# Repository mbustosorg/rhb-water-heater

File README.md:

Red Hot Beverly Water Heater
============================

Controls the water bath's solenoid valve from a DS18B20 in the bath, reads
the loop pressure, and drives a four digit HT16K33 display.  CircuitPython on
a Waveshare ESP32-S3-ETH at 192.168.1.9, wired; there is no WiFi.

The heater relay (`heater_pin`, IO47) is initialised low and never driven;
the heater is controlled elsewhere.

OSC messages
------------

Every address has one producer.  `/pressure` is consumed here, never
re-broadcast.

| Address | Direction | Payload |
| --- | --- | --- |
| `/temperature` | out | Bath temperature, deg F.  The only temperature on the network |
| `/water_heater` | out | Valve open/shut.  Named for the heater it used to switch |
| `/upper_temp`, `/lower_temp` | out | Configured valve setpoints, deg F |
| `/water_pressure` | out | Bath loop pressure, PSI |
| `/pressure` | in, from rhb-sensor-monitor | Accumulator pressure, PSI, rounded |

The outbound messages go every 5 s, in that order, to `MOBILE_CLIENTS`.  Keep
`/water_pressure` last: rhb-sensor-monitor writes its `water_*.csv` row when
it arrives.

microosc dispatches on `startswith`, so `propane_pressure_handler` re-checks
the address to ignore `/pressure_fine`.

Display
-------

| Digits | Shows |
| --- | --- |
| 0-1 | Accumulator pressure, from `/pressure` |
| 2-3 | Bath temperature, blinking while the valve is open |

`--` means no data.

Configuration
-------------

`config_rhb.json`, gitignored.

| Key | Meaning |
| --- | --- |
| `IP` | This device's static address |
| `MOBILE_CLIENTS` | Comma separated listeners, `host` or `host:port` (body display is `192.168.1.3:10002`) |
| `UPPER_TEMP` | Valve shuts at or above, deg F |
| `LOWER_TEMP` | Valve opens at or below, deg F |

Never call `set_dhcp()`: the rig has no DHCP, and it blocks the event loop,
valve included, waiting for a lease.

A listener that fails, usually an absent phone, is skipped for a growing
number of cycles.

Valve control
-------------

| Condition | Action |
| --- | --- |
| Temperature at or below `LOWER_TEMP` | Valve opens |
| Temperature at or above `UPPER_TEMP` | Valve shuts |
| Between the two | No change |
| No usable temperature reading | Valve shuts |

Readings outside 33-212F are discarded; a missing probe used to read as 0F.

The old ten minute recycle safety shutdown policed the heater, which this
board no longer owns, so it was removed.

Hardware
--------

| Pin | Use |
| --- | --- |
| IO47 | Heater SSR, not driven |
| IO48 | Valve SSR |
| IO3 | Safety shutdown SSR |
| IO1 | Loop pressure, analogue |
| IO15 | OneWire, DS18B20 bath probe |
| IO38 / IO39 | I2C SCL / SDA, HT16K33 display |

Powered by PoE alone, on a carrier board; the SSRs are off the board.  See
[HARDWARE.md](HARDWARE.md) and [kicad/](kicad/README.md).  **Set
`PRESSURE_DIVIDER` in `code.py` to 1.5 when the carrier goes in.**

The probe runs at 9 bit: readings are used as whole degrees, and 12 bit
blocks the event loop 750 ms per read instead of 94 ms.

Deployment
----------

Copy `code.py`, `rhb_utils.py` and `config_rhb.json` to `CIRCUITPY`.  The
board soft reboots on write and the relay pins initialise off.

Console: `/dev/cu.usbmodem<UID>` (`cu.*`, not `tty.*`, so DTR is not
asserted).  A healthy board prints `Temperature: NN` about every 5 s.

Known rough edges
-----------------

- `/water_heater` and `state["heater_status"]` report the valve, kept so
  rhb-sensor-monitor and the body display didn't have to change.
- The valve shuts on any unusable probe reading, and the OneWire bus throws
  CRC errors regularly, so a flaky probe cycles the valve.
- The OneWire bus has also returned an empty scan at boot.  The software
  recovers, but suspect the pull-up, parasite power or cable length first.
- `read_and_display_temp` keeps the last probe on the bus, so a second one is
  ignored.  `scan_probes` logs how many it found.
- The receive path overrides microosc's 1 ms socket timeout and 128 byte
  buffer; either default alone stops `/pressure` arriving.  See `poll_osc`.

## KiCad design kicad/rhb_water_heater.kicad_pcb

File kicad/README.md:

Water Heater Carrier Board
==========================

Two layer, 86.5 x 51.5 mm carrier for the circuit in
[HARDWARE.md](../HARDWARE.md).
Parts: [bom.csv](bom.csv).

- **U1** sits component side up, pin 1 (square pad) top right.  Its RJ45 end
  overhangs the right edge by about 16 mm, clearing the cable and PoE module.
- **Terminals**, along the bottom edge, pin 1 (square pad) on the right:

  | Block | Pins, left to right |
  | --- | --- |
  | J7 `PROBE` | `GND DQ 3V3` |
  | J6 `PRESSURE` | `GND SIG +5V` |
  | J5 `SAFETY`, J4 `HEATER`, J3 `VALVE` | `GND SIG` |

- **J2** is `+ - D C`, matching the backpack.
- Ground is poured on both layers.

Regenerating
------------

Edit the scripts, not the KiCad files, then run `./build.sh`, or
`./build.sh --no-route` to try a layout.  Routing needs Java 17+ and
`~/tools/freerouting-1.9.jar`.

| Expected warning | Why |
| --- | --- |
| `lib_symbol_issues` | Symbols live only in the schematic |
| `extra_footprint` | Mounting holes aren't in the schematic |

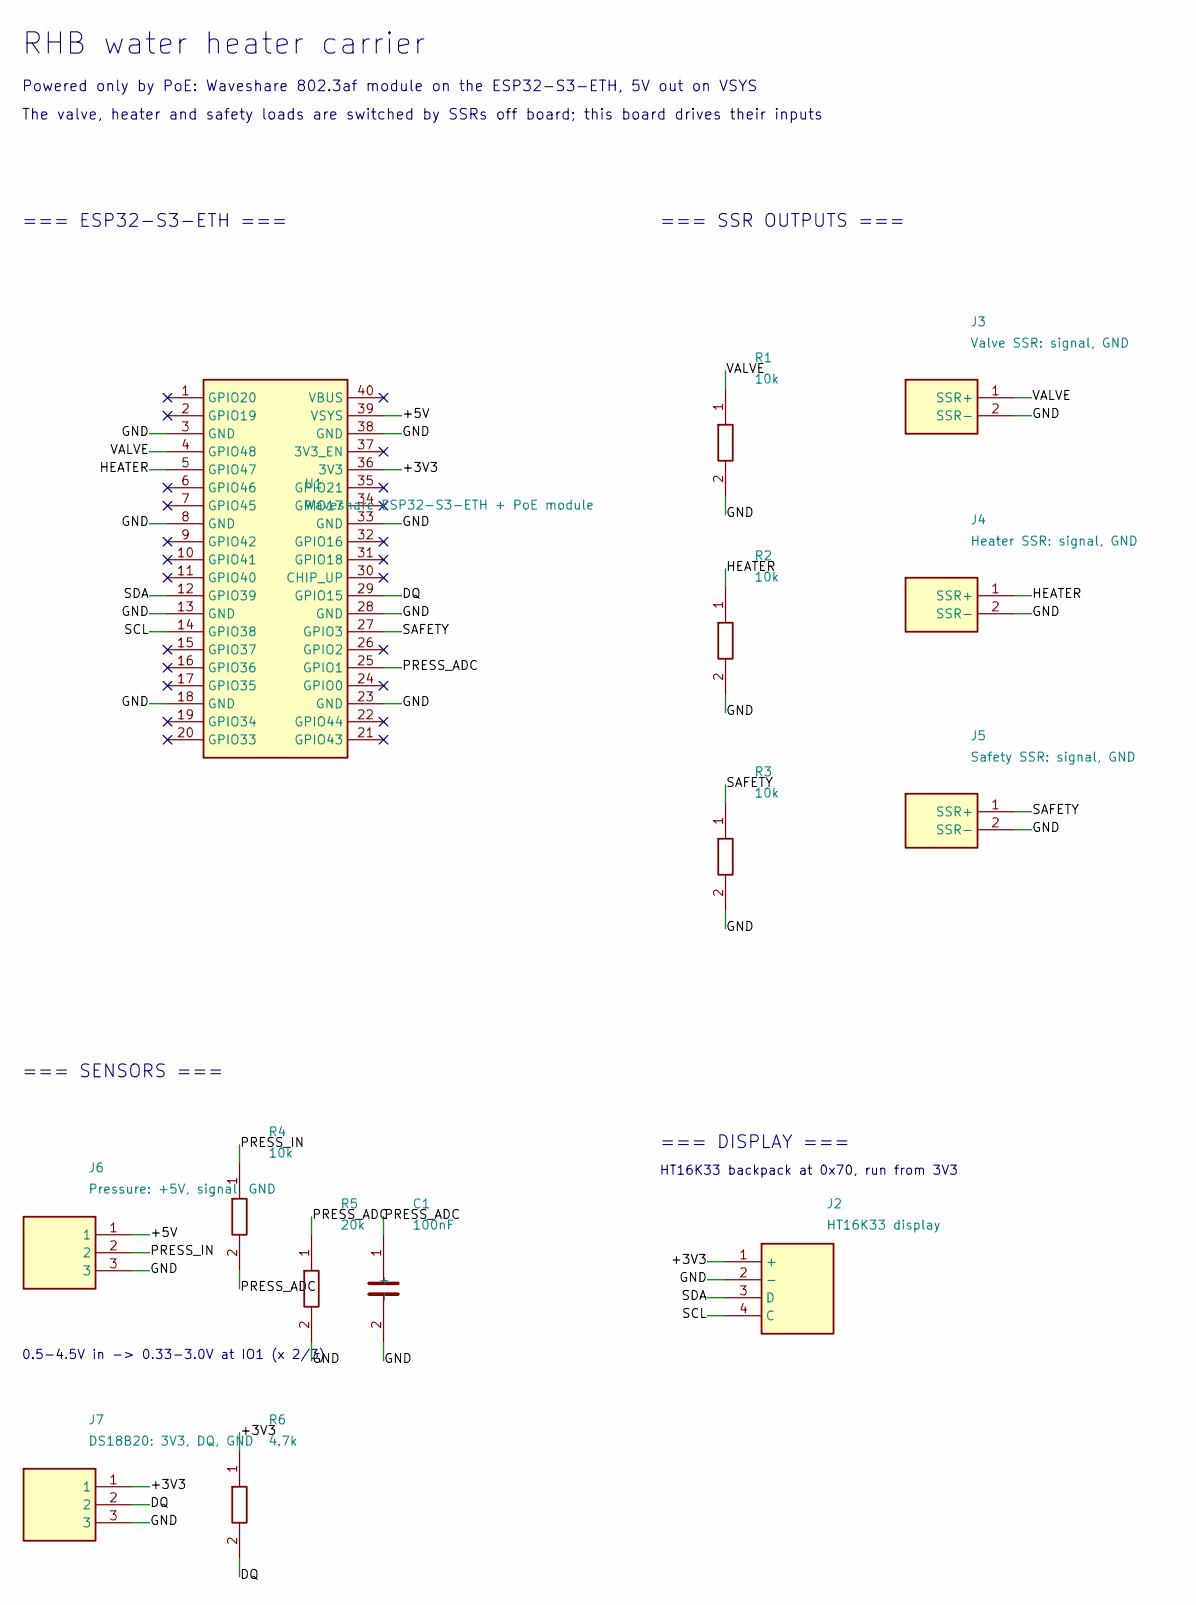
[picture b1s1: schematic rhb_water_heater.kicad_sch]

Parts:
C1: 100nF; C_Disc_D5.0mm_W2.5mm_P5.00mm
J2: HT16K33 display; JST_XH_B4B-XH-A_1x04_P2.50mm_Vertical
J3: Valve SSR: signal, GND; TerminalBlock_Phoenix_MKDS-1,5-2-5.08_1x02_P5.08mm_Horizont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
J4: Heater SSR: signal, GND; TerminalBlock_Phoenix_MKDS-1,5-2-5.08_1x02_P5.08mm_Horizont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
J5: Safety SSR: signal, GND; TerminalBlock_Phoenix_MKDS-1,5-2-5.08_1x02_P5.08mm_Horizont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
J6: Pressure: +5V, signal, GND; TerminalBlock_Phoenix_MKDS-1,5-3-5.08_1x03_P5.08mm_Horizont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
J7: DS18B20: 3V3, DQ, GND; TerminalBlock_Phoenix_MKDS-1,5-3-5.08_1x03_P5.08mm_Horizont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
R1, R2, R3, R4: 10k; R_Axial_DIN0207_L6.3mm_D2.5mm_P2.54mm_Vertical
R5: 20k; R_Axial_DIN0207_L6.3mm_D2.5mm_P2.54mm_Vertical
R6: 4.7k; R_Axial_DIN0207_L6.3mm_D2.5mm_P2.54mm_Vertical
U1: Waveshare ESP32-S3-ETH + PoE module; Waveshare_ESP32-S3-ETH_Socketed

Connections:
/+3V3: J2.1 (+), J7.1, R6.1, U1.36 (3V3)
/+5V: J6.1, U1.39 (VSYS)
/DQ: J7.2, R6.2, U1.29 (GPIO15)
/GND: C1.2 (-), J2.2 (-), J3.2 (SSR-), J4.2 (SSR-), J5.2 (SSR-), J6.3, J7.3, R1.2, R2.2, R3.2, R5.2, U1.3 (GND), U1.8 (GND), U1.13 (GND), U1.18 (GND), U1.23 (GND), U1.28 (GND), U1.33 (GND), U1.38 (GND)
/HEATER: J4.1 (SSR+), R2.1, U1.5 (GPIO47)
/PRESS_ADC: C1.1 (+), R4.2, R5.1, U1.25 (GPIO1)
/PRESS_IN: J6.2, R4.1
/SAFETY: J5.1 (SSR+), R3.1, U1.27 (GPIO3)
/SCL: J2.4 (C), U1.14 (GPIO38)
/SDA: J2.3 (D), U1.12 (GPIO39)
/VALVE: J3.1 (SSR+), R1.1, U1.4 (GPIO48)

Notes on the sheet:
RHB water heater carrier
Powered only by PoE: Waveshare 802.3af module on the ESP32-S3-ETH, 5V out on VSYS
The valve, heater and safety loads are switched by SSRs off board; this board drives their inputs
=== ESP32-S3-ETH ===
=== SSR OUTPUTS ===
=== SENSORS ===
0.5-4.5V in -> 0.33-3.0V at IO1 (x 2/3)
=== DISPLAY ===
HT16K33 backpack at 0x70, run from 3V3

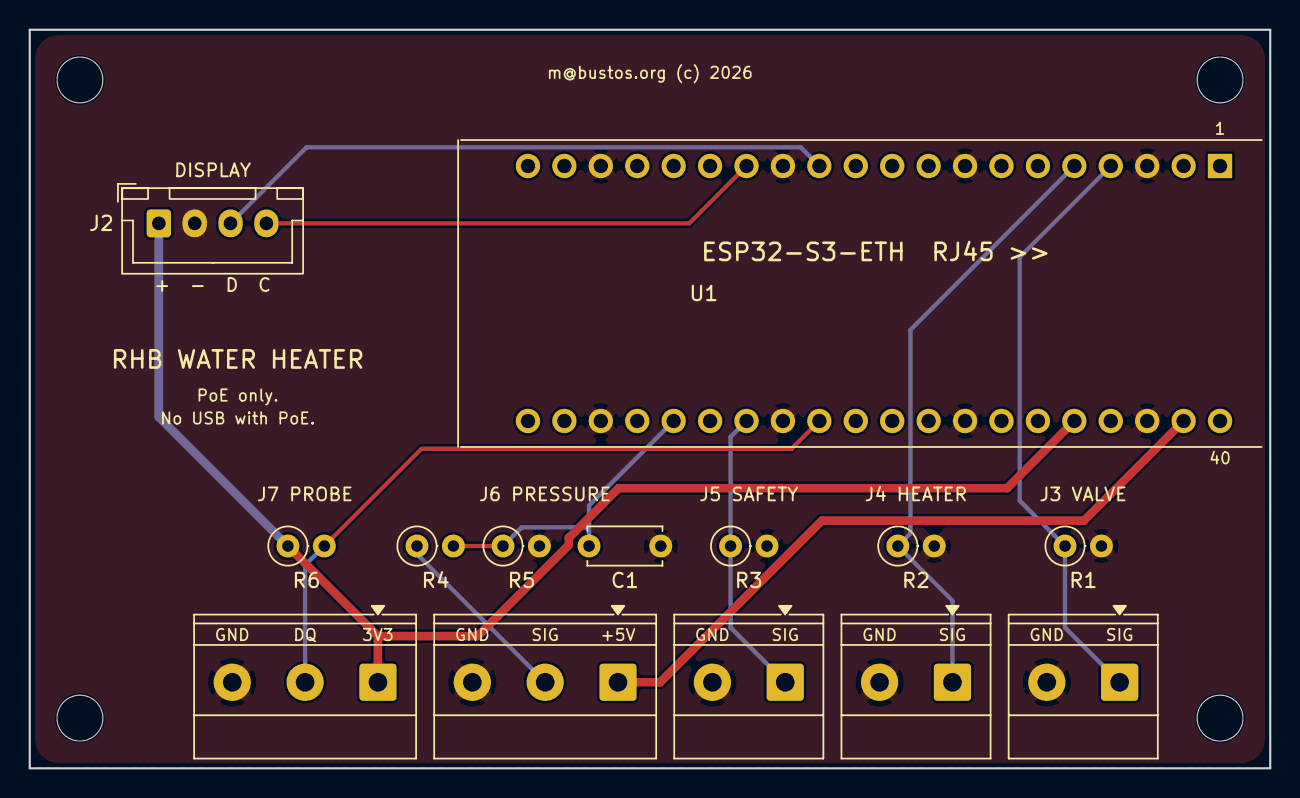
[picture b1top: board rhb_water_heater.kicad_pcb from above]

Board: 2 copper layers, 86.5 x 51.5 mm, 18 parts (0 on the bottom side), 11 nets.

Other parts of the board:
H1, H2, H3, H4: M3; MountingHole_3.2mm_M3

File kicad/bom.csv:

Ref,Qty,Value,Description,Manufacturer,MPN,Notes
U1,1,ESP32-S3-POE-ETH,"ESP32-S3 module with W5500 Ethernet and PoE, Pico-style 2x20 header",Waveshare,ESP32-S3-POE-ETH,Or an ESP32-S3-ETH with Waveshare's PoE module
,2,1x20 female,"Pin socket 1x20, 2.54 mm, through-hole (U1 sockets)",,,
R1-R4,4,10k,"Resistor, 1/4 W, axial, standing",,,R4 1% metal film
R5,1,20k,"Resistor, 1/4 W, axial, standing, 1% metal film",,,
R6,1,4.7k,"Resistor, 1/4 W, axial, standing",,,DS18B20 pull-up
C1,1,100nF,"Ceramic disc, 5 mm pitch",,,
J3-J5,3,Screw terminal 2 way,"Terminal block, 5.08 mm",Phoenix Contact,1715721,"Valve, heater, safety SSRs"
J6-J7,2,Screw terminal 3 way,"Terminal block, 5.08 mm",Phoenix Contact,1715734,"Pressure transducer, DS18B20 probe"
J2,1,JST-XH 4 pin,"Header, 2.50 mm, vertical",JST,B4B-XH-A(LF)(SN),To the HT16K33 display

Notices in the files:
kicad/rhb_water_heater.kicad_pcb:
m@bustos.org (c) 2026
